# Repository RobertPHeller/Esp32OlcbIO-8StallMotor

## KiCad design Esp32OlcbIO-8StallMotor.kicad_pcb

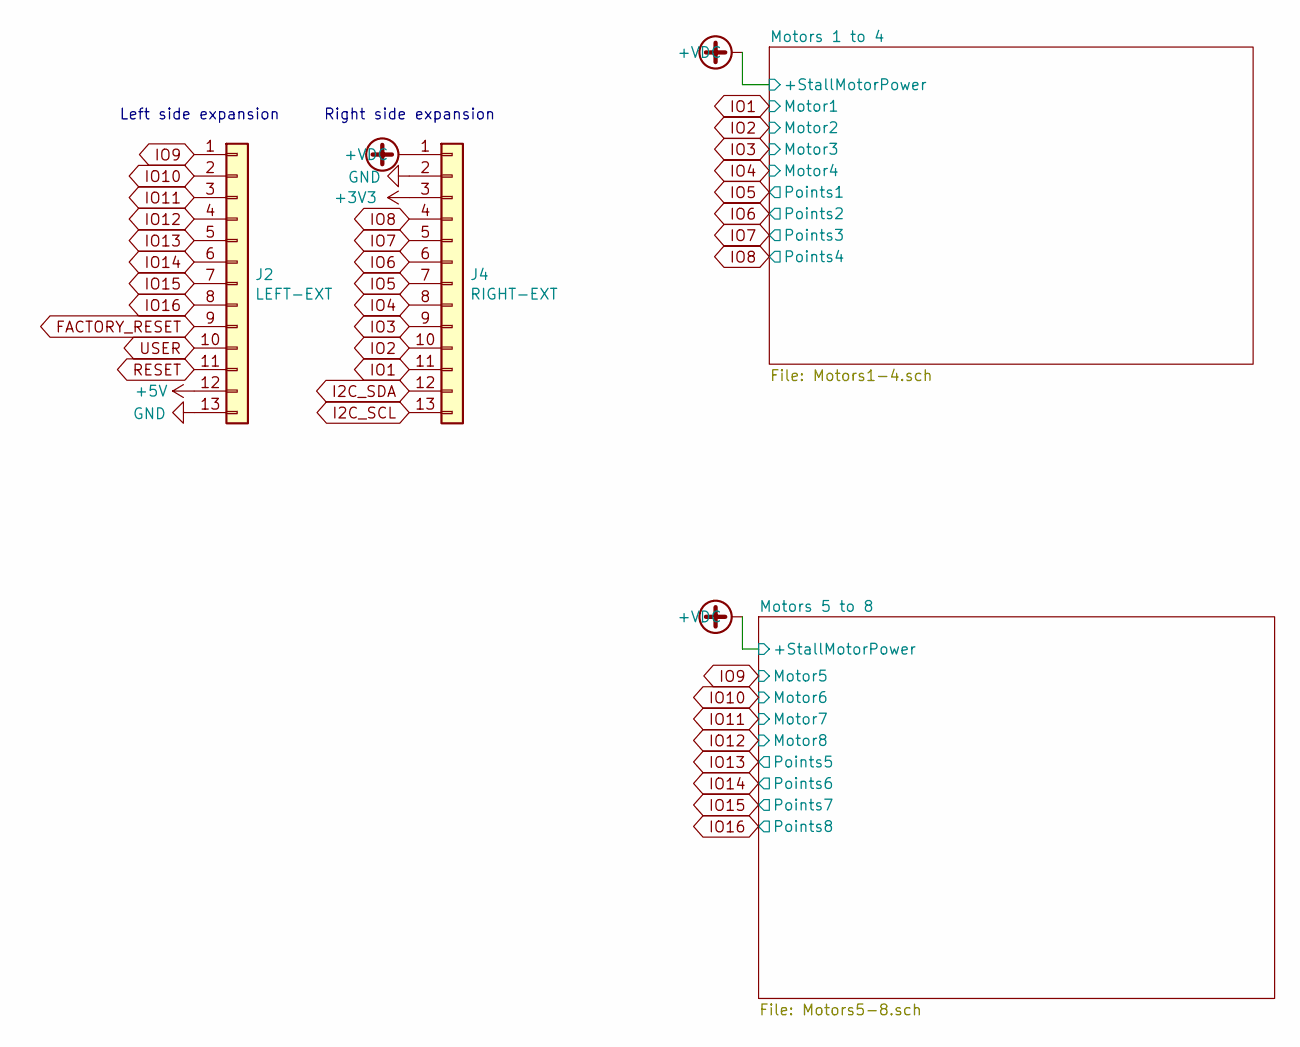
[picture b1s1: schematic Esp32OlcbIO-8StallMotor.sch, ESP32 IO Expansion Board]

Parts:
J2: LEFT-EXT; PinHeader_1x13_P2.54mm_Vertical
J4: RIGHT-EXT; PinHeader_1x13_P2.54mm_Vertical

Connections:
+3V3: J4.3; also elsewhere on the board
+5V: J2.12
+VDC: J4.1; also elsewhere on the board
FACTORY_RESET: J2.9
GND: J2.13, J4.2; also elsewhere on the board
I2C_SCL: J4.13
I2C_SDA: J4.12
IO1: J4.11; also elsewhere on the board
IO2: J4.10; also elsewhere on the board
IO3: J4.9; also elsewhere on the board
IO4: J4.8; also elsewhere on the board
IO5: J4.7; also elsewhere on the board
IO6: J4.6; also elsewhere on the board
IO7: J4.5; also elsewhere on the board
IO8: J4.4; also elsewhere on the board
IO9: J2.1; also elsewhere on the board
IO10: J2.2; also elsewhere on the board
IO11: J2.3; also elsewhere on the board
IO12: J2.4; also elsewhere on the board
IO13: J2.5; also elsewhere on the board
IO14: J2.6; also elsewhere on the board
IO15: J2.7; also elsewhere on the board
IO16: J2.8; also elsewhere on the board
RESET: J2.11
USER: J2.10

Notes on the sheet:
Left side expansion
Right side expansion

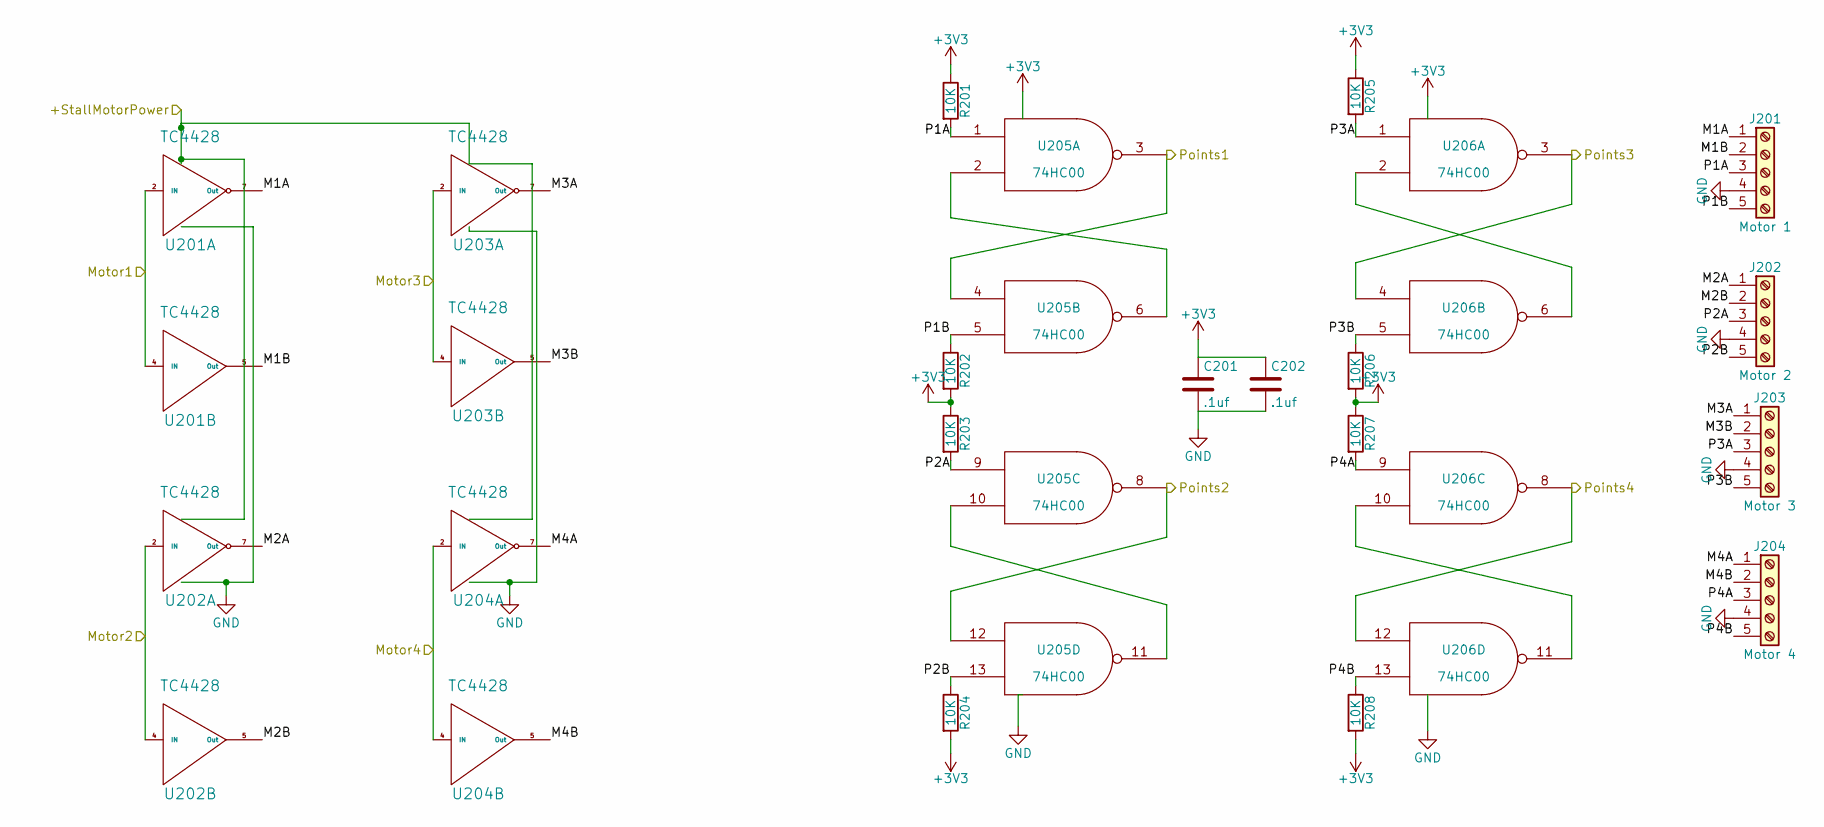
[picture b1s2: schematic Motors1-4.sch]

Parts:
C201, C202: .1uf; C_0603_HandSoldering
J201: Motor 1; TerminalBlock_Pheonix_MPT-2.54mm_5pol
J202: Motor 2; TerminalBlock_Pheonix_MPT-2.54mm_5pol
J203: Motor 3; TerminalBlock_Pheonix_MPT-2.54mm_5pol
J204: Motor 4; TerminalBlock_Pheonix_MPT-2.54mm_5pol
R201, R202, R203, R204, R205, R206, R207, R208: 10K; R_0603_HandSoldering
U201, U202, U203, U204: TC4428; SOIC-8_3.9x4.9mm_Pitch1.27mm
U205, U206: 74HC00; SOIC-14_3.9x8.7mm_Pitch1.27mm

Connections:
+3V3: C201.1, C202.1, R201.1, R202.2, R203.1, R204.2, R205.1, R206.2, R207.1, R208.2, U205.14 (VCC), U206.14 (VCC); also elsewhere on the board
+VDC: U201.6 (Vdd), U202.6 (Vdd), U203.6 (Vdd), U204.6 (Vdd); also elsewhere on the board
/Motors 1 to 4/M1A: J201.1, U201.7 (Out)
/Motors 1 to 4/M1B: J201.2, U201.5 (Out)
/Motors 1 to 4/M2A: J202.1, U202.7 (Out)
/Motors 1 to 4/M2B: J202.2, U202.5 (Out)
/Motors 1 to 4/M3A: J203.1, U203.7 (Out)
/Motors 1 to 4/M3B: J203.2, U203.5 (Out)
/Motors 1 to 4/M4A: J204.1, U204.7 (Out)
/Motors 1 to 4/M4B: J204.2, U204.5 (Out)
/Motors 1 to 4/P1A: J201.3, R201.2, U205.1
/Motors 1 to 4/P1B: J201.5, R202.1, U205.5
/Motors 1 to 4/P2A: J202.3, R203.2, U205.9
/Motors 1 to 4/P2B: J202.5, R204.1, U205.13
/Motors 1 to 4/P3A: J203.3, R205.2, U206.1
/Motors 1 to 4/P3B: J203.5, R206.1, U206.5
/Motors 1 to 4/P4A: J204.3, R207.2, U206.9
/Motors 1 to 4/P4B: J204.5, R208.1, U206.13
GND: C201.2, C202.2, J201.4, J202.4, J203.4, J204.4, U201.3 (GND), U202.3 (GND), U203.3 (GND), U204.3 (GND), U205.7 (GND), U206.7 (GND); also elsewhere on the board
IO1: U201.2 (IN), U201.4 (IN); also elsewhere on the board
IO2: U202.2 (IN), U202.4 (IN); also elsewhere on the board
IO3: U203.2 (IN), U203.4 (IN); also elsewhere on the board
IO4: U204.2 (IN), U204.4 (IN); also elsewhere on the board
IO5: U205.3, U205.4; also elsewhere on the board
IO6: U205.8, U205.12; also elsewhere on the board
IO7: U206.3, U206.4; also elsewhere on the board
IO8: U206.8, U206.12; also elsewhere on the board
unnamed: U205.2, U205.6
unnamed: U205.10, U205.11
unnamed: U206.2, U206.6
unnamed: U206.10, U206.11

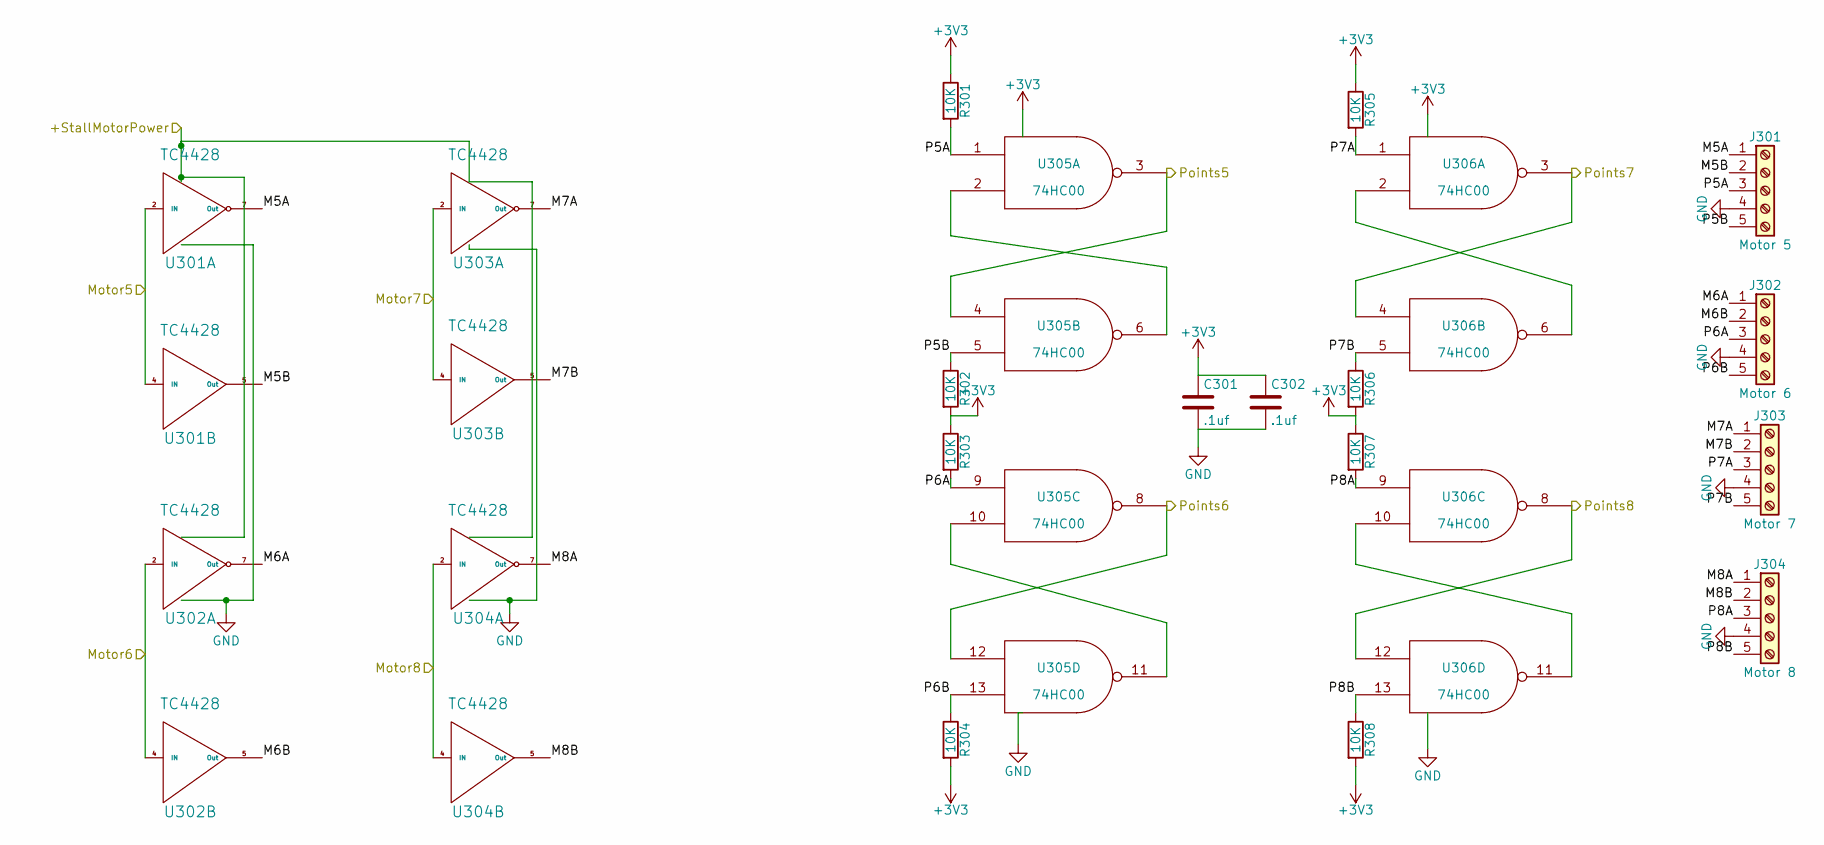
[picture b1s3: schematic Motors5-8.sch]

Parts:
C301, C302: .1uf; C_0603_HandSoldering
J301: Motor 5; TerminalBlock_Pheonix_MPT-2.54mm_5pol
J302: Motor 6; TerminalBlock_Pheonix_MPT-2.54mm_5pol
J303: Motor 7; TerminalBlock_Pheonix_MPT-2.54mm_5pol
J304: Motor 8; TerminalBlock_Pheonix_MPT-2.54mm_5pol
R301, R302, R303, R304, R305, R306, R307, R308: 10K; R_0603_HandSoldering
U301, U302, U303, U304: TC4428; SOIC-8_3.9x4.9mm_Pitch1.27mm
U305, U306: 74HC00; SOIC-14_3.9x8.7mm_Pitch1.27mm

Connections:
+3V3: C301.1, C302.1, R301.1, R302.2, R303.1, R304.2, R305.1, R306.2, R307.1, R308.2, U305.14 (VCC), U306.14 (VCC); also elsewhere on the board
+VDC: U301.6 (Vdd), U302.6 (Vdd), U303.6 (Vdd), U304.6 (Vdd); also elsewhere on the board
/Motors 5 to 8/M5A: J301.1, U301.7 (Out)
/Motors 5 to 8/M5B: J301.2, U301.5 (Out)
/Motors 5 to 8/M6A: J302.1, U302.7 (Out)
/Motors 5 to 8/M6B: J302.2, U302.5 (Out)
/Motors 5 to 8/M7A: J303.1, U303.7 (Out)
/Motors 5 to 8/M7B: J303.2, U303.5 (Out)
/Motors 5 to 8/M8A: J304.1, U304.7 (Out)
/Motors 5 to 8/M8B: J304.2, U304.5 (Out)
/Motors 5 to 8/P5A: J301.3, R301.2, U305.1
/Motors 5 to 8/P5B: J301.5, R302.1, U305.5
/Motors 5 to 8/P6A: J302.3, R303.2, U305.9
/Motors 5 to 8/P6B: J302.5, R304.1, U305.13
/Motors 5 to 8/P7A: J303.3, R305.2, U306.1
/Motors 5 to 8/P7B: J303.5, R306.1, U306.5
/Motors 5 to 8/P8A: J304.3, R307.2, U306.9
/Motors 5 to 8/P8B: J304.5, R308.1, U306.13
GND: C301.2, C302.2, J301.4, J302.4, J303.4, J304.4, U301.3 (GND), U302.3 (GND), U303.3 (GND), U304.3 (GND), U305.7 (GND), U306.7 (GND); also elsewhere on the board
IO9: U301.2 (IN), U301.4 (IN); also elsewhere on the board
IO10: U302.2 (IN), U302.4 (IN); also elsewhere on the board
IO11: U303.2 (IN), U303.4 (IN); also elsewhere on the board
IO12: U304.2 (IN), U304.4 (IN); also elsewhere on the board
IO13: U305.3, U305.4; also elsewhere on the board
IO14: U305.8, U305.12; also elsewhere on the board
IO15: U306.3, U306.4; also elsewhere on the board
IO16: U306.8, U306.12; also elsewhere on the board
unnamed: U305.2, U305.6
unnamed: U305.10, U305.11
unnamed: U306.2, U306.6
unnamed: U306.10, U306.11

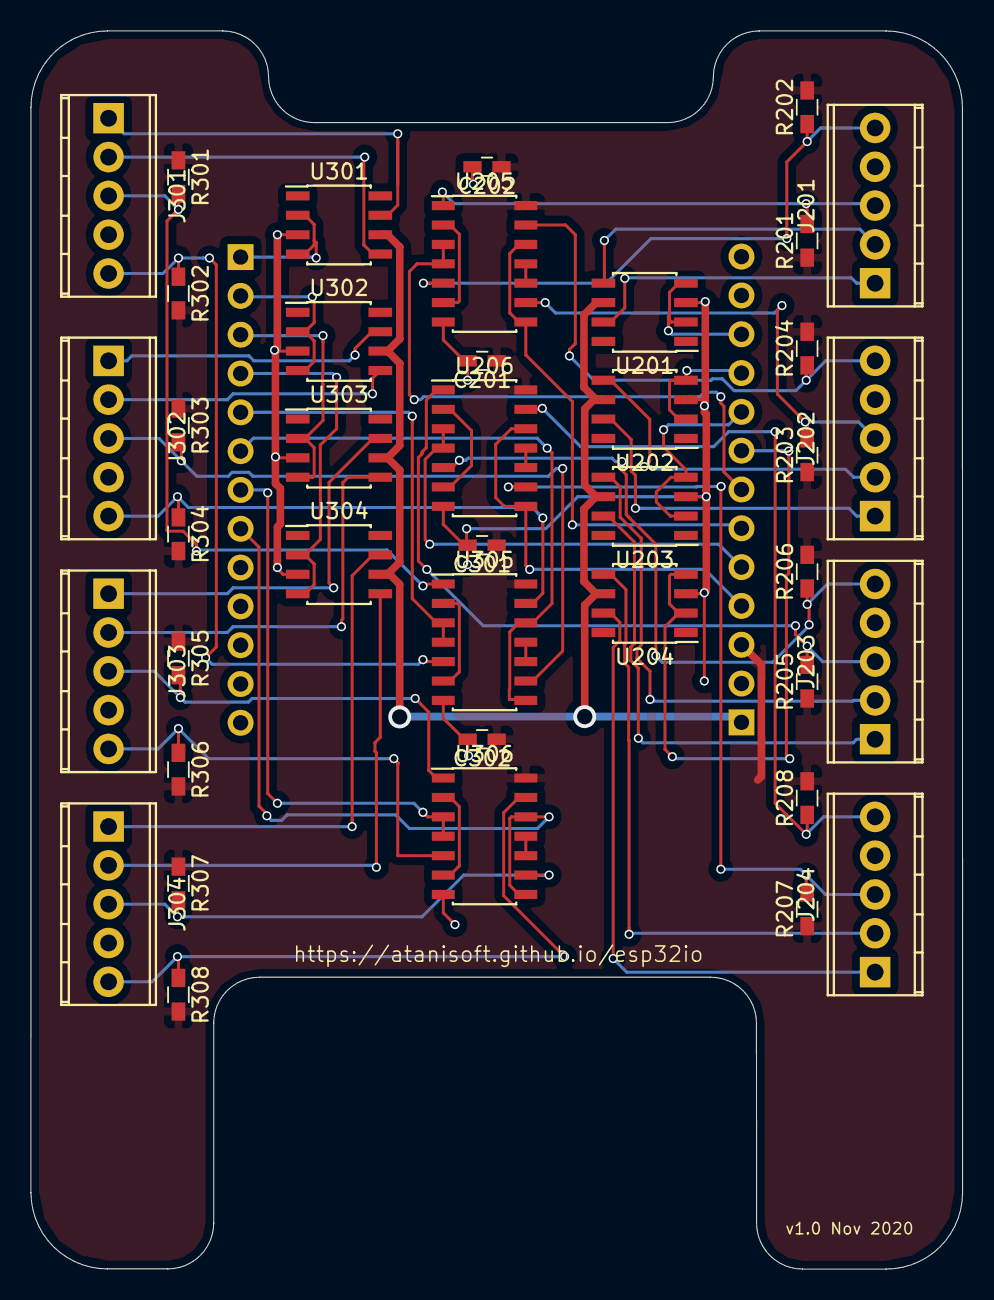
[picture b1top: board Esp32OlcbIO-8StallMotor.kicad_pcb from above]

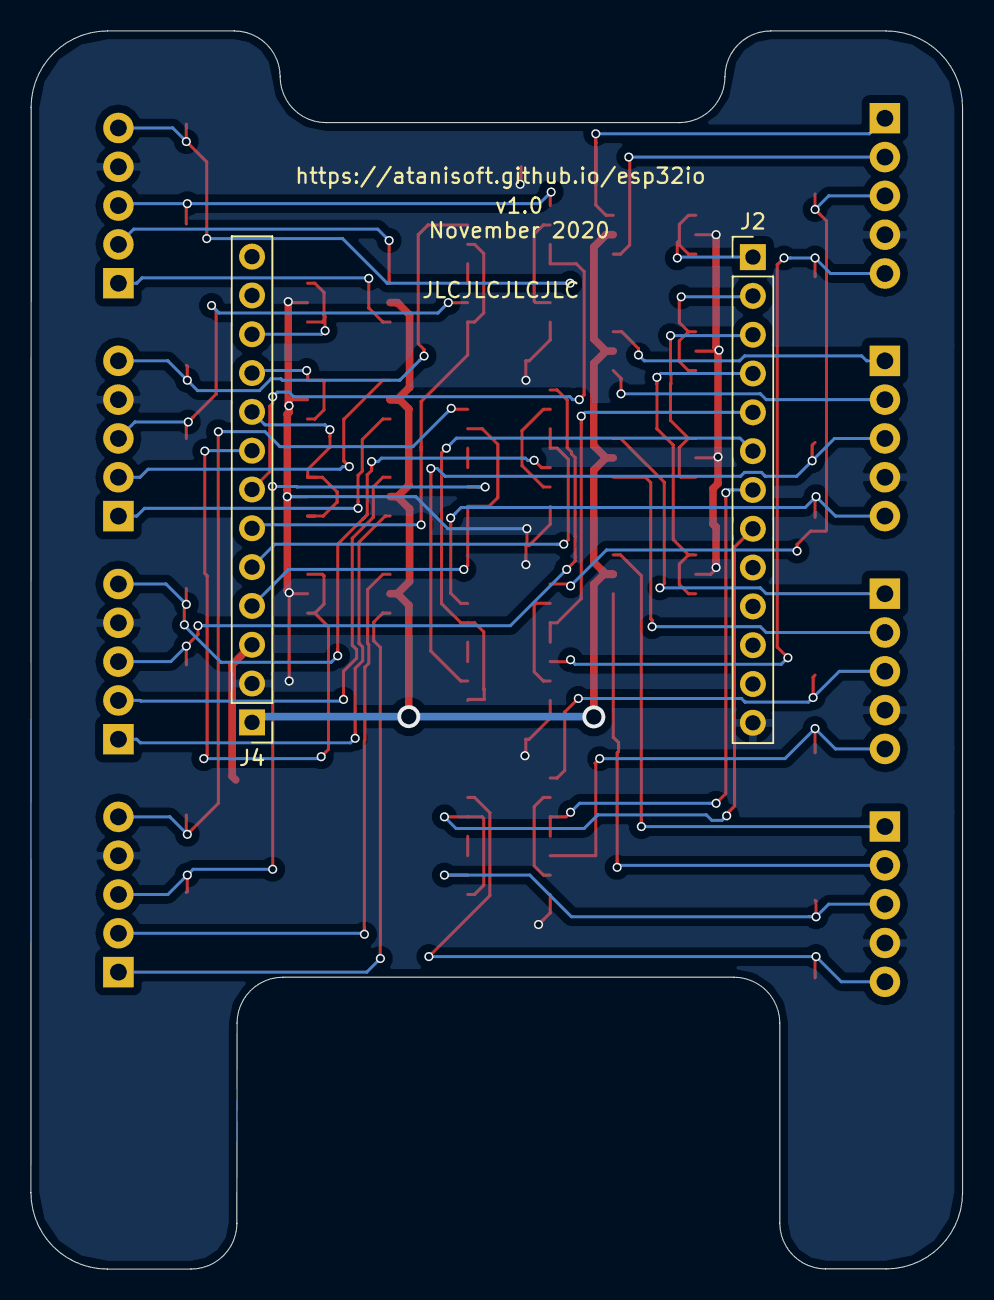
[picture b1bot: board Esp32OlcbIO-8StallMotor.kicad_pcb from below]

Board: 2 copper layers, 61.0 x 81.0 mm, 42 parts (2 on the bottom side), 59 nets.

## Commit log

2023-01-14 Completed Schematic.
2023-01-14 Component Placement.
2023-01-15 Completed Board.
